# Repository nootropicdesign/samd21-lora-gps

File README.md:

# SAMD21 LoRa GPS Module

This repo has example code for the [SAMD21-based LoRa GPS development board described here](https://nootropicdesign.com/projectlab/2018/10/27/samd21-lora-gps).
This board can be programmed with Arduino as an Arduino Zero. The board uses a SAMD21E18A microcontroller which has fewer pins than the 'G' variant of this chip used on the Arduino Zero, and the Arduino Zero pins used for SPI are not present in this package. The way to get around this is to either define a new Arduino core for this chip variant, or to define a new SPI interface on pins that we do have. I want to program this chip as an ordinary Arduino Zero, so I defined a new SPI interface called `SPI1` according to [this Adafruit tutorial](https://learn.adafruit.com/using-atsamd21-sercom-to-add-more-spi-i2c-serial-ports/creating-a-new-spi).

This required some modifications to certain libraries, described below.

### RadioGPSTest

Simple example demonstrating the use of the Quectel L80 GPS module and HopeRF LoRa module. The files `RHHardwareSPI1.cpp` and `RHHardwareSPI1.h` extend the RadioHead library so that it can use the SPI1 interface defined in the sketch by this code:
```
#ifdef USE_SPI1
SPIClass SPI1(&sercom1, 12, 13, 11, SPI_PAD_0_SCK_1, SERCOM_RX_PAD_3);
RH_RF95 rf95(SS, DIO0, hardware_spi1);
#else
```

Dependencies:

* [RadioHead library](http://www.airspayce.com/mikem/arduino/RadioHead/) - Powerful Arduino library for a variety of radio modules
* [Adafruit GPS library](https://github.com/adafruit/Adafruit_GPS) - Arduino GPS library for NMEA sentence parsing

### LoRaWANTestABP

LoRaWAN node that uses the ABP method of connecting to a gateway. While considered less secure, this method connects much faster and is more reliable.
[See the project description here](https://nootropicdesign.com/projectlab/2018/10/28/lorawan-end-devices/).

Dependencies:

* [arduino-lmic library](https://github.com/nootropicdesign/arduino-lmic) - LoRaWAN stack for embedded devices. This fork of the library has been modified to support the SPI1 interface used by the SAMD21E.
* [CayenneLPP library](https://github.com/sabas1080/CayenneLPP) - Cayenne low-power payload for efficient packing of GPS data into LoRaWAN packets
* [Adafruit GPS library](https://github.com/adafruit/Adafruit_GPS) - Arduino GPS library for NMEA sentence parsing

### LoRaWANTestOTAA

LoRaWAN node that uses the over-the-air activation (OTAA) method of connecting to a gateway.
[See the project description here](https://nootropicdesign.com/projectlab/2018/10/28/lorawan-end-devices/).

* [arduino-lmic library](https://github.com/nootropicdesign/arduino-lmic) - LoRaWAN stack for embedded devices. This fork of the library has been modified to support the SPI1 interface used by the SAMD21E.
* [CayenneLPP library](https://github.com/sabas1080/CayenneLPP) - Cayenne low-power payload for efficient packing of GPS data into LoRaWAN packets
* [Adafruit GPS library](https://github.com/adafruit/Adafruit_GPS) - Arduino GPS library for NMEA sentence parsing

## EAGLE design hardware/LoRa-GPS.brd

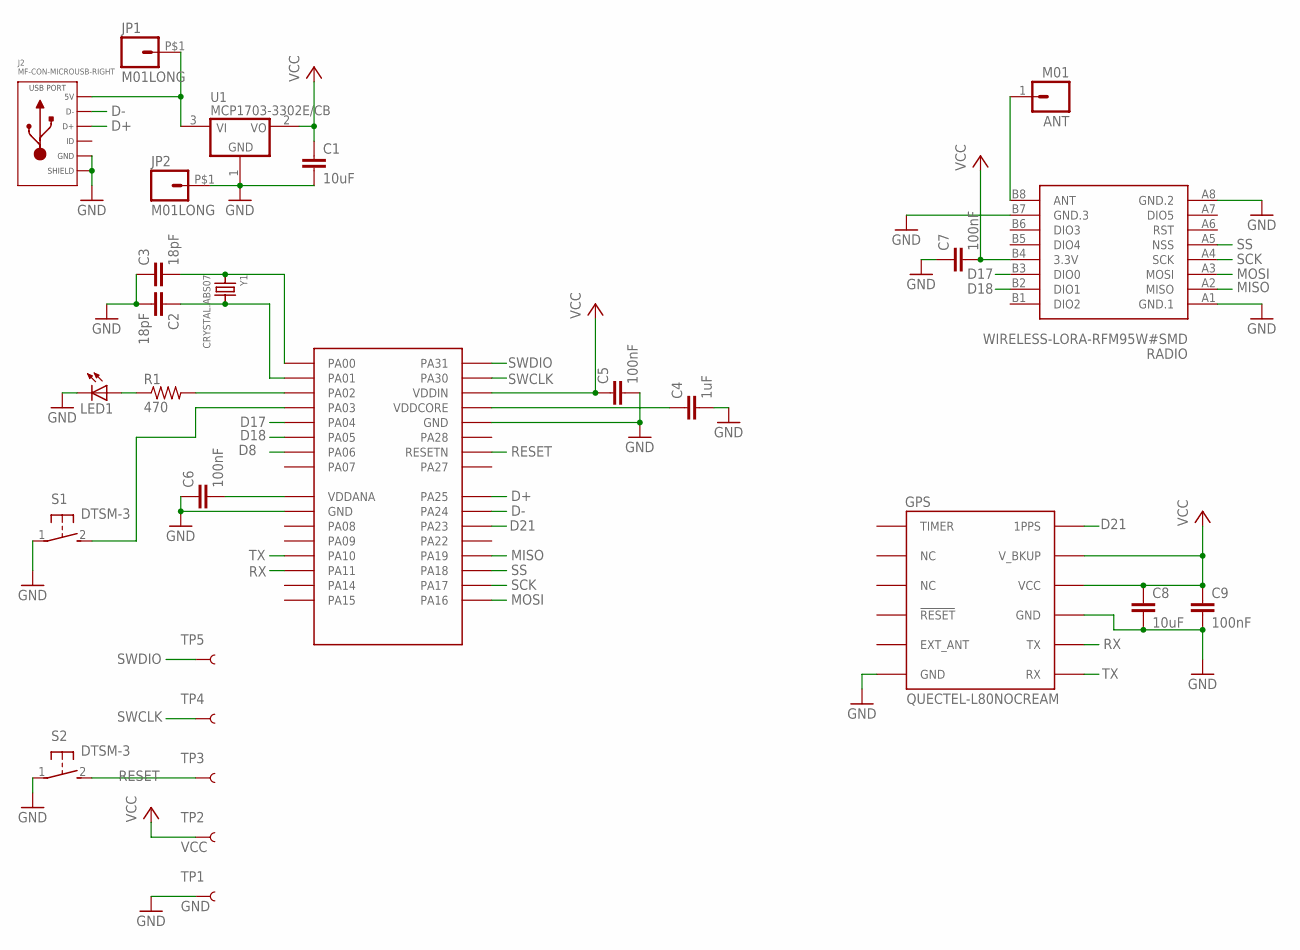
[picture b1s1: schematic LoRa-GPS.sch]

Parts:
ANT: M01; 1X01
C1, C8: 10uF; C0603-THINCREAM
C2, C3: 18pF; C0603-THINCREAM
C4: 1uF; C0603-THINCREAM
C5, C6, C7, C9: 100nF; C0603-THINCREAM
GPS: QUECTEL-L80NOCREAM; QUECTEL-L80-NOCREAM
J2: MF-CON-MICROUSB-RIGHT; MICROUSB-RIGHT
JP1, JP2: M01LONG; 1X01_LONG
LED1: LEDCHIPLED_0805_THINCREAM; CHIPLED_0805-THINCREAM
R1: 470; R0603-THINCREAM
RADIO: WIRELESS-LORA-RFM95W#SMD
S1, S2: DTSM-3
SAMD21: ATSAMD21E18A-AU; 32-TQFP
TP1: GND; TP_15TH
TP2: VCC; PAD.03X.05
TP3, TP4, TP5: TEST-POINT3X5; PAD.03X.05
U1: MCP1703-3302E/CB; SOT23A_MICROCHIP_CB
Y1: CRYSTAL.ABS07; ABS07

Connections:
ANT: ANT.1, RADIO.B8 (ANT)
D8: SAMD21.7 (PA06)
D17: RADIO.B3 (DIO0), SAMD21.5 (PA04)
D18: RADIO.B2 (DIO1), SAMD21.6 (PA05)
D21: GPS.6 (1PPS), SAMD21.22 (PA23)
D+: J2.3 (D+), SAMD21.24 (PA25)
D-: J2.2 (D-), SAMD21.23 (PA24)
GND: C1.2, C2.2, C3.1, C4.2, C5.2, C6.1, C7.1, C8.2, C9.2, GPS.3 (GND), GPS.12 (GND), J2.5 (GND), J2.S1 (SLD), J2.S2 (SLD), J2.S3 (SLD), J2.S4 (SLD), JP2.P$1, LED1.C, RADIO.A1 (GND.1), RADIO.A8 (GND.2), RADIO.B7 (GND.3), S1.1, S2.1, SAMD21.10 (GND), SAMD21.28 (GND), TP1.P$1, U1.1 (GND)
MISO: RADIO.A2 (MISO), SAMD21.20 (PA19)
MOSI: RADIO.A3 (MOSI), SAMD21.17 (PA16)
unnamed: C6.2, SAMD21.9 (VDDANA)
unnamed: C2.1, SAMD21.2 (PA01), Y1.2
unnamed: C3.2, SAMD21.1 (PA00), Y1.1
unnamed: LED1.A, R1.1
unnamed: C4.1, SAMD21.29 (VDDCORE)
unnamed: R1.2, SAMD21.3 (PA02)
unnamed: S1.2, SAMD21.4 (PA03)
RESET: S2.2, SAMD21.26 (RESETN), TP3.P$1
RX: GPS.2 (TX), SAMD21.14 (PA11)
SCK: RADIO.A4 (SCK), SAMD21.18 (PA17)
SS: RADIO.A5 (NSS), SAMD21.19 (PA18)
SWCLK: SAMD21.31 (PA30), TP4.P$1
SWDIO: SAMD21.32 (PA31), TP5.P$1
TX: GPS.1 (RX), SAMD21.13 (PA10)
VCC: C1.1, C5.1, C7.2, C8.1, C9.1, GPS.4 (VCC), GPS.5 (V_BKUP), RADIO.B4 (3.3V), SAMD21.30 (VDDIN), TP2.P$1, U1.2 (VO)
VIN: J2.1 (5V), JP1.P$1, U1.3 (VI)

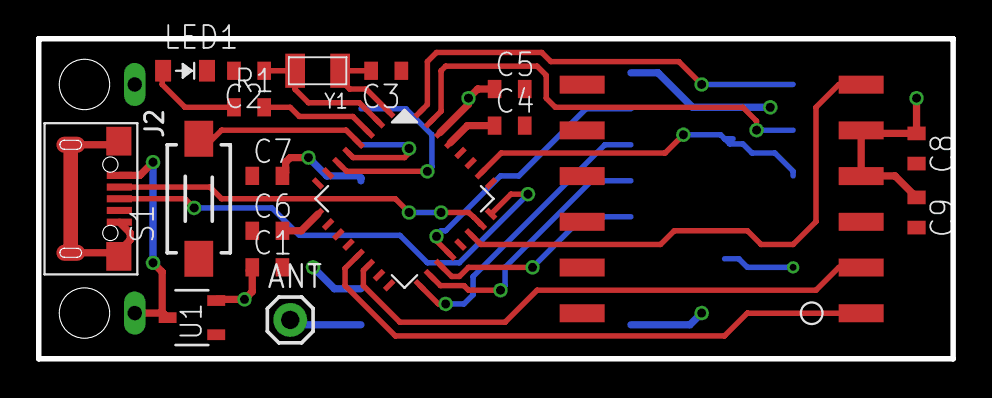
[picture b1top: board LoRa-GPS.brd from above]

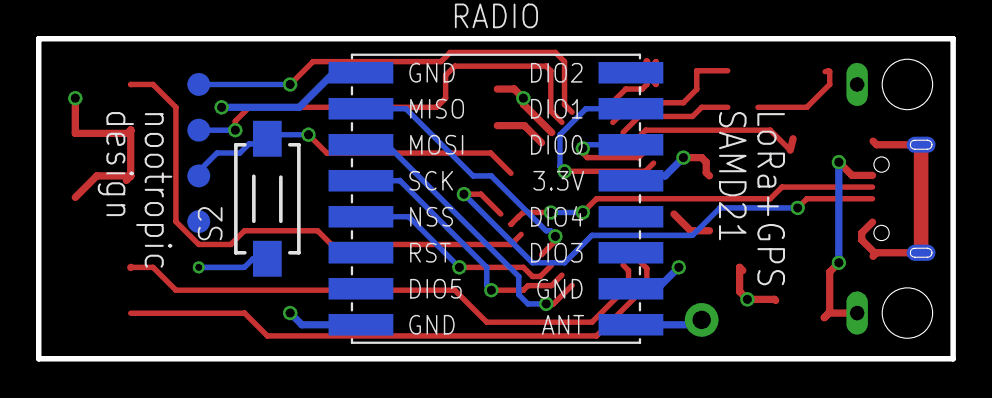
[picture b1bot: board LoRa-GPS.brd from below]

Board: 2 copper layers, 50.8 x 17.8 mm, 27 parts (6 on the bottom side), 25 nets.

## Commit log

2018-10-27 Initial repo.
2018-10-28 Updated project links.

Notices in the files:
parts and their libraries:
diy-modules: Released under the Creative Commons Attribution 4.0 International License: http://creativecommons.org/licenses/by/4.0
SparkFun-Passives: Licensing: Creative Commons ShareAlike 4.0 International - https://creativecommons.org/licenses/by-sa/4.0
